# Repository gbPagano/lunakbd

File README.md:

# Lunakbd

A split wireless keyboard inspired by the [Corne](https://github.com/foostan/crkbd) and the [Sofle](https://github.com/josefadamcik/SofleKeyboard): schematic and PCB in KiCad, case in FreeCAD, and firmware built on [RMK](https://github.com/HaoboGu/rmk), running on nRF52840 promicro controllers.

The two halves connect over BLE to a central USB dongle currently under development.

## Repository layout

| Path                                       | Contents                                                           |
| ------------------------------------------ | ------------------------------------------------------------------ |
| [`pcb/`](pcb)                              | KiCad project, schematic and PCB                                   |
| [`libraries/`](libraries)                  | Custom KiCad symbol/footprint library (`lunalib`)                  |
| [`layout/`](layout)                        | Keyboard layout definitions (KLE JSON)                             |
| [`case/`](case)                            | FreeCAD sources, STEP exports and printable 3MFs                   |
| [`models/`](models)                        | 3D models used in the assembly                                     |
| [`firmware/`](firmware)                    | Rust/RMK firmware - see [`firmware/README.md`](firmware/README.md) |
| [`photos/`](photos), [`renders/`](renders) | Build photos and renders                                           |

## License

Copyright (C) 2025-2026 gbPagano

This project is licensed under the GNU General Public License as published
by the Free Software Foundation, either version 3 of the License, or (at
your option) any later version - see the [`LICENSE`](LICENSE) file for the
full license text.

It is distributed in the hope that it will be useful, but WITHOUT ANY
WARRANTY; without even the implied warranty of MERCHANTABILITY or FITNESS
FOR A PARTICULAR PURPOSE.

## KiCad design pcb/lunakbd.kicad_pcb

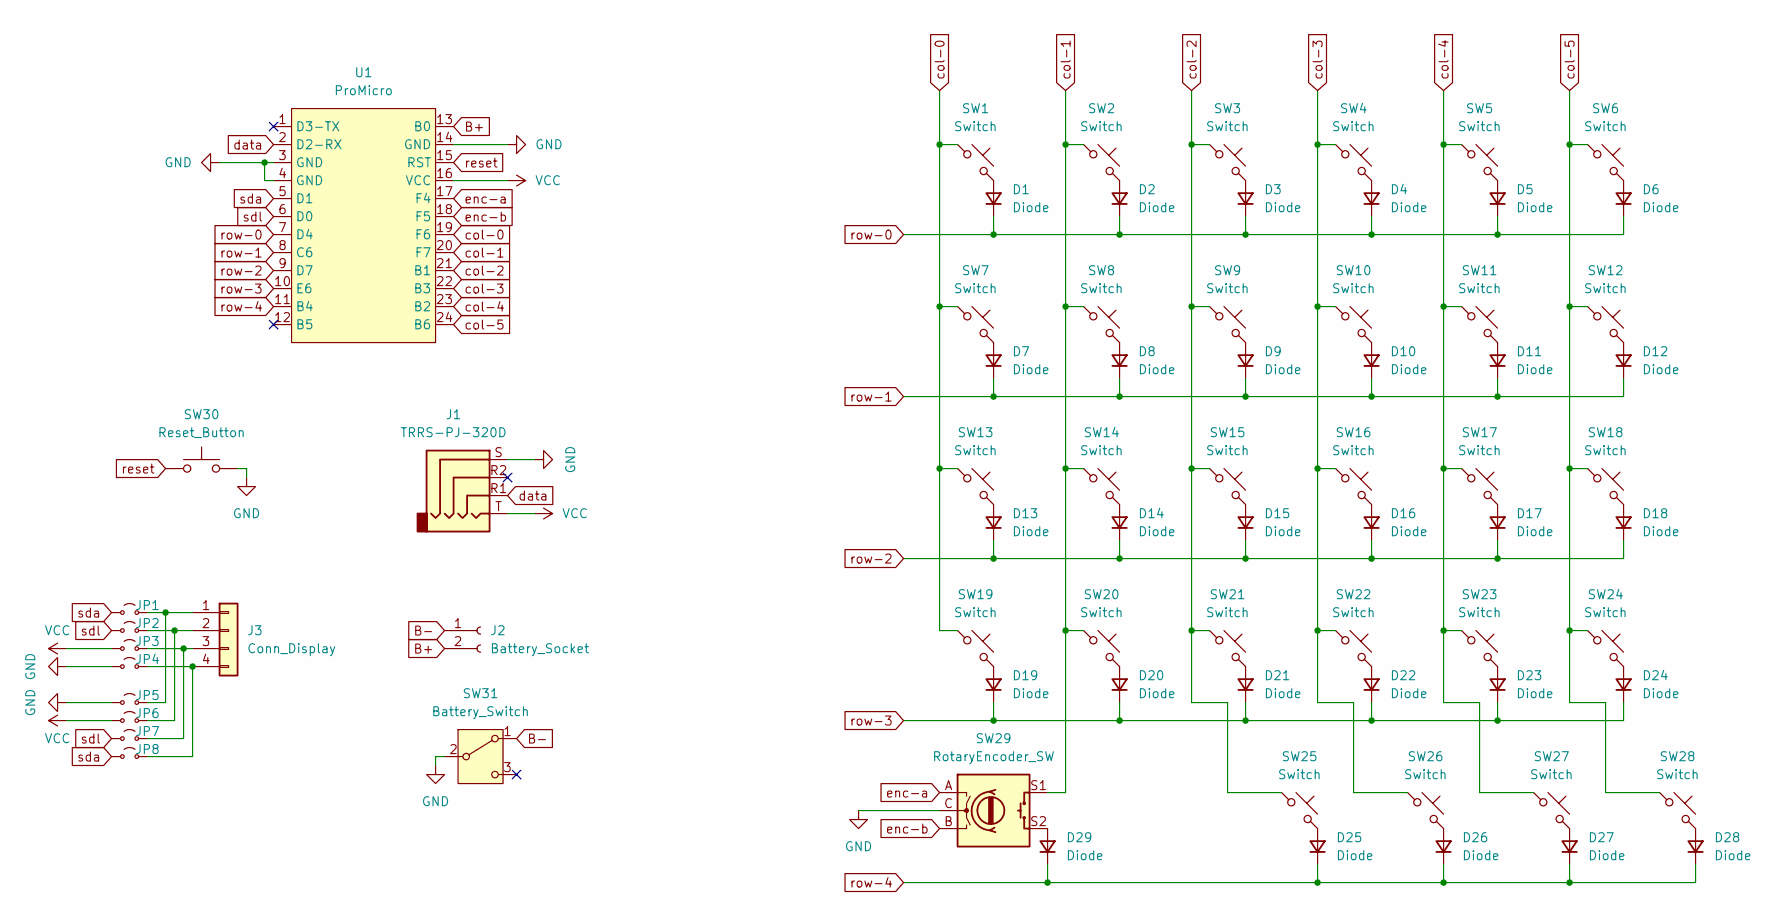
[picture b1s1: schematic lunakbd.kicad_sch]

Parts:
D1, D2, D3, D4, D5, D6, D7, D8, D9, D10, D11, D12, D13, D14, D15, D16, D17, D18, D19, D20, D21, D22, D23, D24, D25, D26, D27, D28, D29: Diode; D_SOD-123
J1: TRRS-PJ-320D
J2: Battery_Socket; JST_PH_S2B-PH-K_1x02_P2.00mm_Horizontal
J3: Conn_Display; OLED
JP1, JP2, JP3, JP4, JP5, JP6, JP7, JP8: Jumper; SolderJumper-2_P1.3mm_Open_RoundedPad1.0x1.5mm
SW1, SW2, SW3, SW4, SW5, SW6, SW7, SW8, SW9, SW10, SW11, SW12, SW13, SW14, SW15, SW16, SW17, SW18, SW19, SW20, SW21, SW22, SW23, SW24, SW25, SW26, SW27: Switch; SW_Hotswap_Kailh_MX_1.00u
SW28: Switch; SW_Hotswap_Kailh_MX_1.25u_90deg
SW29: RotaryEncoder_SW; RotaryEncoder_Alps_EC11E-Switch_Vertical_H20mm
SW30: Reset_Button; SW-SMD_SHOU_TS36CA-0.6
SW31: Battery_Switch; SW_MSK12C02-HB
U1: ProMicro; SuperMini_nRF52840

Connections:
B+: J2.2, U1.13 (B0)
B-: J2.1, SW31.1 (A)
GND: J1.S, JP4.1 (A), JP5.1 (A), SW29.C, SW30.2, SW31.2 (B), U1.3 (GND), U1.4 (GND), U1.14 (GND)
unnamed: D1.2 (A), SW1.2
unnamed: D2.2 (A), SW2.2
unnamed: D3.2 (A), SW3.2
unnamed: D4.2 (A), SW4.2
unnamed: D5.2 (A), SW5.2
unnamed: D6.2 (A), SW6.2
unnamed: D7.2 (A), SW7.2
unnamed: D8.2 (A), SW8.2
unnamed: D9.2 (A), SW9.2
unnamed: D10.2 (A), SW10.2
unnamed: D11.2 (A), SW11.2
unnamed: D12.2 (A), SW12.2
unnamed: D13.2 (A), SW13.2
unnamed: D14.2 (A), SW14.2
unnamed: D15.2 (A), SW15.2
unnamed: D16.2 (A), SW16.2
unnamed: D17.2 (A), SW17.2
unnamed: D18.2 (A), SW18.2
unnamed: D19.2 (A), SW19.2
unnamed: D20.2 (A), SW20.2
unnamed: D21.2 (A), SW21.2
unnamed: D22.2 (A), SW22.2
unnamed: D23.2 (A), SW23.2
unnamed: D24.2 (A), SW24.2
unnamed: D25.2 (A), SW25.2
unnamed: D26.2 (A), SW26.2
unnamed: D27.2 (A), SW27.2
unnamed: D28.2 (A), SW28.2
unnamed: D29.2 (A), SW29.S2
unnamed: J3.1, JP1.2 (B), JP5.2 (B)
unnamed: J3.2, JP2.2 (B), JP6.2 (B)
unnamed: J3.3, JP3.2 (B), JP7.2 (B)
unnamed: J3.4, JP4.2 (B), JP8.2 (B)
VCC: J1.T, JP3.1 (A), JP6.1 (A), U1.16 (VCC)
col-0: SW1.1, SW7.1, SW13.1, SW19.1, U1.19 (F6)
col-1: SW2.1, SW8.1, SW14.1, SW20.1, SW29.S1, U1.20 (F7)
col-2: SW3.1, SW9.1, SW15.1, SW21.1, SW25.1, U1.21 (B1)
col-3: SW4.1, SW10.1, SW16.1, SW22.1, SW26.1, U1.22 (B3)
col-4: SW5.1, SW11.1, SW17.1, SW23.1, SW27.1, U1.23 (B2)
col-5: SW6.1, SW12.1, SW18.1, SW24.1, SW28.1, U1.24 (B6)
data: J1.R1, U1.2 (D2-RX)
enc-a: SW29.A, U1.17 (F4)
enc-b: SW29.B, U1.18 (F5)
reset: SW30.1, U1.15 (RST)
row-0: D1.1 (K), D2.1 (K), D3.1 (K), D4.1 (K), D5.1 (K), D6.1 (K), U1.7 (D4)
row-1: D7.1 (K), D8.1 (K), D9.1 (K), D10.1 (K), D11.1 (K), D12.1 (K), U1.8 (C6)
row-2: D13.1 (K), D14.1 (K), D15.1 (K), D16.1 (K), D17.1 (K), D18.1 (K), U1.9 (D7)
row-3: D19.1 (K), D20.1 (K), D21.1 (K), D22.1 (K), D23.1 (K), D24.1 (K), U1.10 (E6)
row-4: D25.1 (K), D26.1 (K), D27.1 (K), D28.1 (K), D29.1 (K), U1.11 (B4)
sda: JP1.1 (A), JP8.1 (A), U1.5 (D1)
sdl: JP2.1 (A), JP7.1 (A), U1.6 (D0)

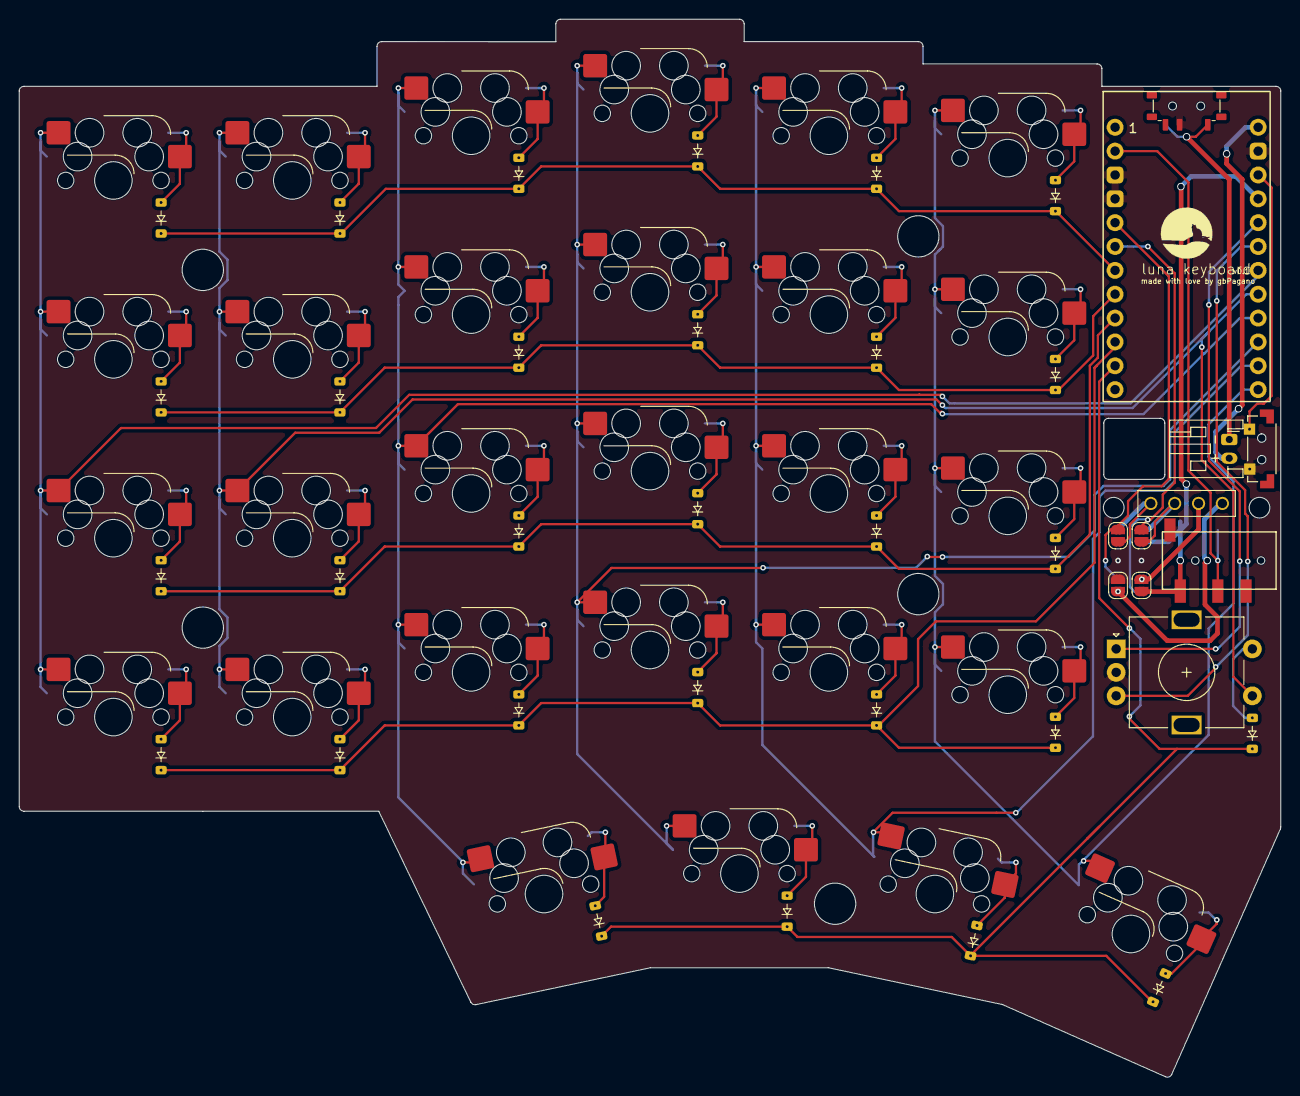
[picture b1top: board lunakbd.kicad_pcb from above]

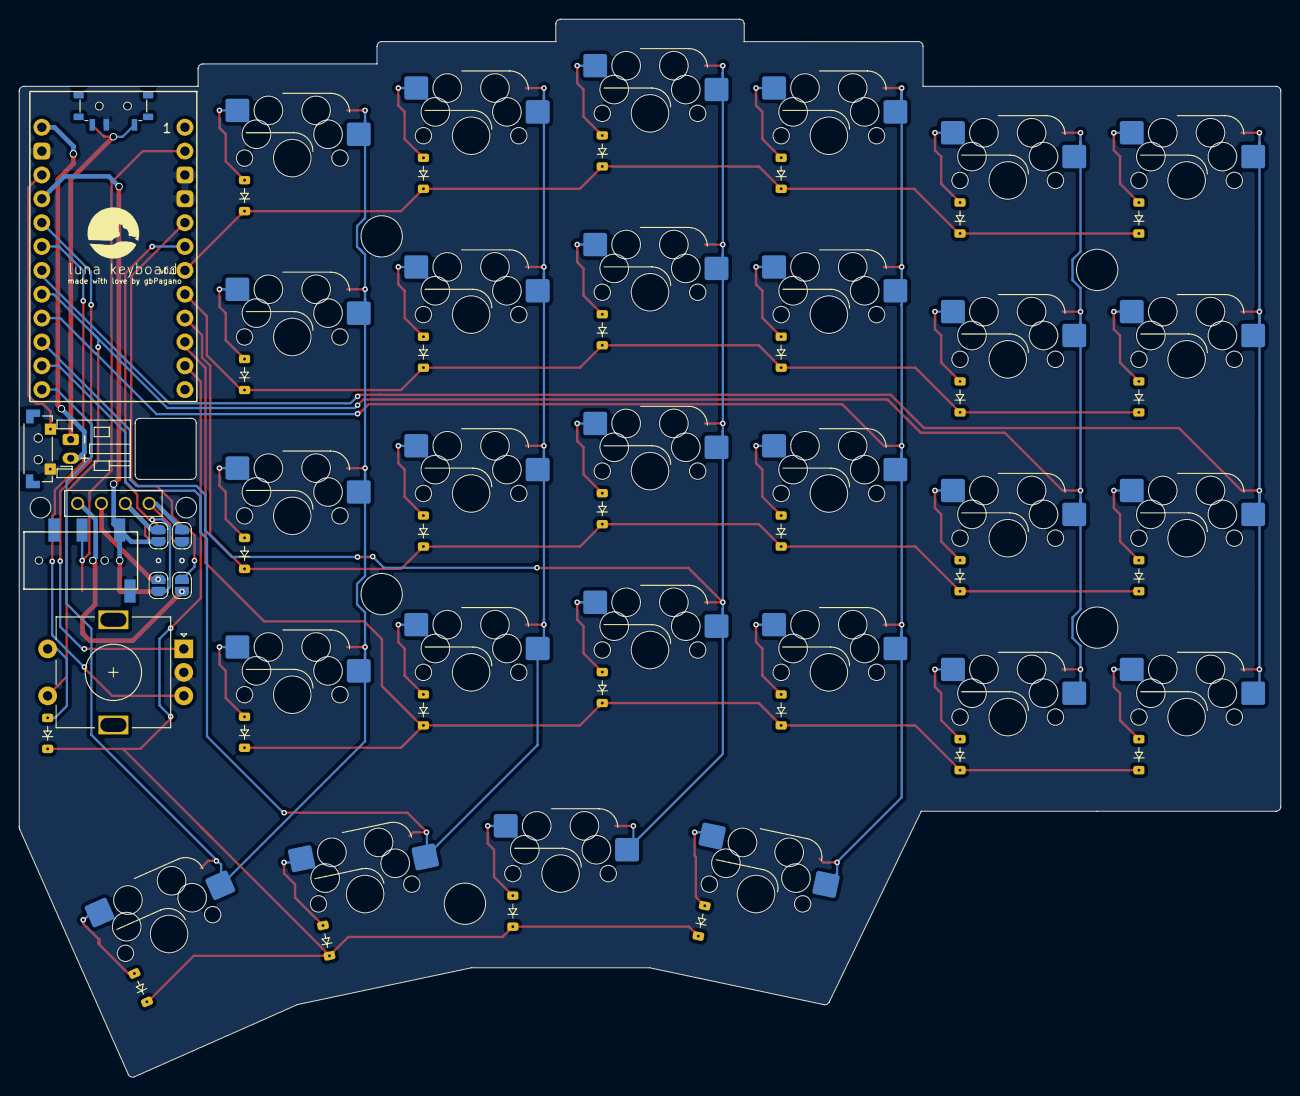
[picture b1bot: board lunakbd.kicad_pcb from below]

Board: 2 copper layers, 134.4 x 112.7 mm, 72 parts (33 on the bottom side), 54 nets.

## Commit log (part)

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2025-04-15 feat: create initial layout
2025-04-16 feat: pcb layout adjustments
2025-04-19 fix: update switch numberation in pcb editor
2025-04-19 feat: complete schematic design
2025-04-21 feat: create edge cuts for pcb
2025-04-22 feat: update footprints and place promicro and oled display
2025-04-23 feat: place rotatory encoder and centralize oled display
2025-04-26 feat: place trrs, battery socket and reset button
2025-04-27 feat: update diode positions
2025-04-27 feat: make all footprints inversibles
2025-04-28 feat: trace routes
2025-04-29 feat: create ground zone
2025-04-30 fix: connection for oled inversion
2025-05-02 refactor: update all footprints and fix thumb keys align
2025-05-03 fix: reset button footprint
2025-05-03 fix: clearence errors
2025-05-03 feat: add logo silkscreen
2025-05-04 fix: add f.mask on promicro pads
2025-11-27 feat: add firmware
2025-11-27 fix: typo in encoder configuration
    closes #1
2025-11-27 feat: update tap hold config

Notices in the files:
README.md:
License: GPL-3.0-or-later
